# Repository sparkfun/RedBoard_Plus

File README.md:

SparkFun RedBoard Plus
============================

[*SparkFun RedBoard Plus (DEV-18158)*](https://www.sparkfun.com/products/18158)

At SparkFun we continually like to innovate, update, and improve even when it comes to our very own development boards. The SparkFun RedBoard Plus is an Arduino-compatible development board that has everything you need in an Arduino Uno with *many* extra perks. The best part about the RedBoard Plus is that it utilizes our handy Qwiic Connect System which means no soldering or shields are required to connect it to the rest of your system!

We've applied every lesson we've learned about making a better Arduino Uno and created the RedBoard Plus! The SparkFun RedBoard Plus has all of the hardware peripherals you know and love: 22x Digital I/O pins with 6x PWM pins, 8x analog pins, UART, I<sup>2</sup>C, SPI, and external interrupts. We've also broken out the SDA, SCL and IOREF pins that showed up on the Arduino Uno R3 footprint, so the RedBoard Plus is compatible with future shields (if you choose to use them). Two additional analog pins are included for A6 and A7.

The USB-to-serial is now done with a *reversible* USB-C connector with through hole anchoring and the ubiquitous CH340G requiring fewer driver installs. The power portion of the RedBoard Plus has been optimized: we use the AP2112 3.3V voltage regulator to provide up to 600mA to daisy chain multiple Qwiic boards and sensors, with full thermal and reverse circuit protection, and added extra decoupling capacitance to increase the sensitivity of the ADC readings. We've also increased the PTC from 500mA to 2A. We've decreased the brightness of the power LED, pin 13 LED, and the TX/RX LEDs from blinding to just perfect.

We've included 3.3V voltage translation and a [Qwiic connector](https://www.sparkfun.com/qwiic) to the edge of the board to allow for quick and seamless connection to our ever-growing line of I<sup>2</sup>C based [Qwiic products](https://www.sparkfun.com/qwiic#products). Jumpers are included on the board for the A4 and A5 pins which are tied directly to the I<sup>2</sup>C bus and can be used to disconnect the logic level converters from the pins. 

For more advanced users we've added an I/O voltage switch also known as the "Red Squirrel" switch (because they are the one [who petitioned for the mod](https://www.sparkfun.com/products/retired/15296#comment-5d78452ec6a6ff5bfc77dba7)). Now you can easily select the GPIO voltage between 3.3V or 5V with just your finger. This is extremely handy if you have a shield or 3.3V sensitive devices, such as an SPI interface, that needs protecting. Worried about accidentally flipping the switch? A piece of tape will lock it in place!

We include clearly labeled PTH holes alongside the standard female headers. This makes it very easy to solder wires in place for a secure connection to make your project 'backpack safe' once you get it working. Solder pads are included on the bottom of the board for USB data pins D+/D- so you can embed your RedBoard Plus into a project and run an external USB connection. We've increased the height of the reset button. This doesn't sound like much, but everyone who's touched it loves the improvement. 

The SparkFun RedBoard Plus can be programmed over a USB-C cable using the Arduino IDE: Just plug in the board, select "**Arduino UNO**" from the board menu and you're ready to upload code! You can power the SparkFun RedBoard Plus over USB or through the barrel jack. The on-board power regulator can handle anything from 7VDC to 15VDC. Check out the related items below for a compatible wall-wart power supply.

Not sure which Arduino or Arduino-compatible board is right for you? Check out our [Arduino Buying Guide](https://www.sparkfun.com/arduino_guide)!

Repository Contents
-------------------
* **/Documentation** - Data sheets, additional product information
* **/Hardware** - Eagle design files (.brd, .sch)
* **/Production** - Production panel files (.brd)

Documentation
--------------
* **[Hookup Guide](https://learn.sparkfun.com/tutorials/1758)** - Basic hookup guide for the RedBoard Plus.

License Information
-------------------

This product is _**open source**_! 

Please review the LICENSE.md file for license information. 

If you have any questions or concerns on licensing, please contact technical support on our [SparkFun forums](https://forum.sparkfun.com/viewforum.php?f=152).

Distributed as-is; no warranty is given.

- Your friends at SparkFun.

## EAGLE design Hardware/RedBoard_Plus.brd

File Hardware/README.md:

SparkFun RedBoard Plus Design Files
=====================================

The .sch and .brd files hare are Eagle CAD schematic and PCB design files from SparkFun Electronics.
A freeware version of Eagle can be found [here](http://www.cadsoftusa.com/download-eagle/freeware/).

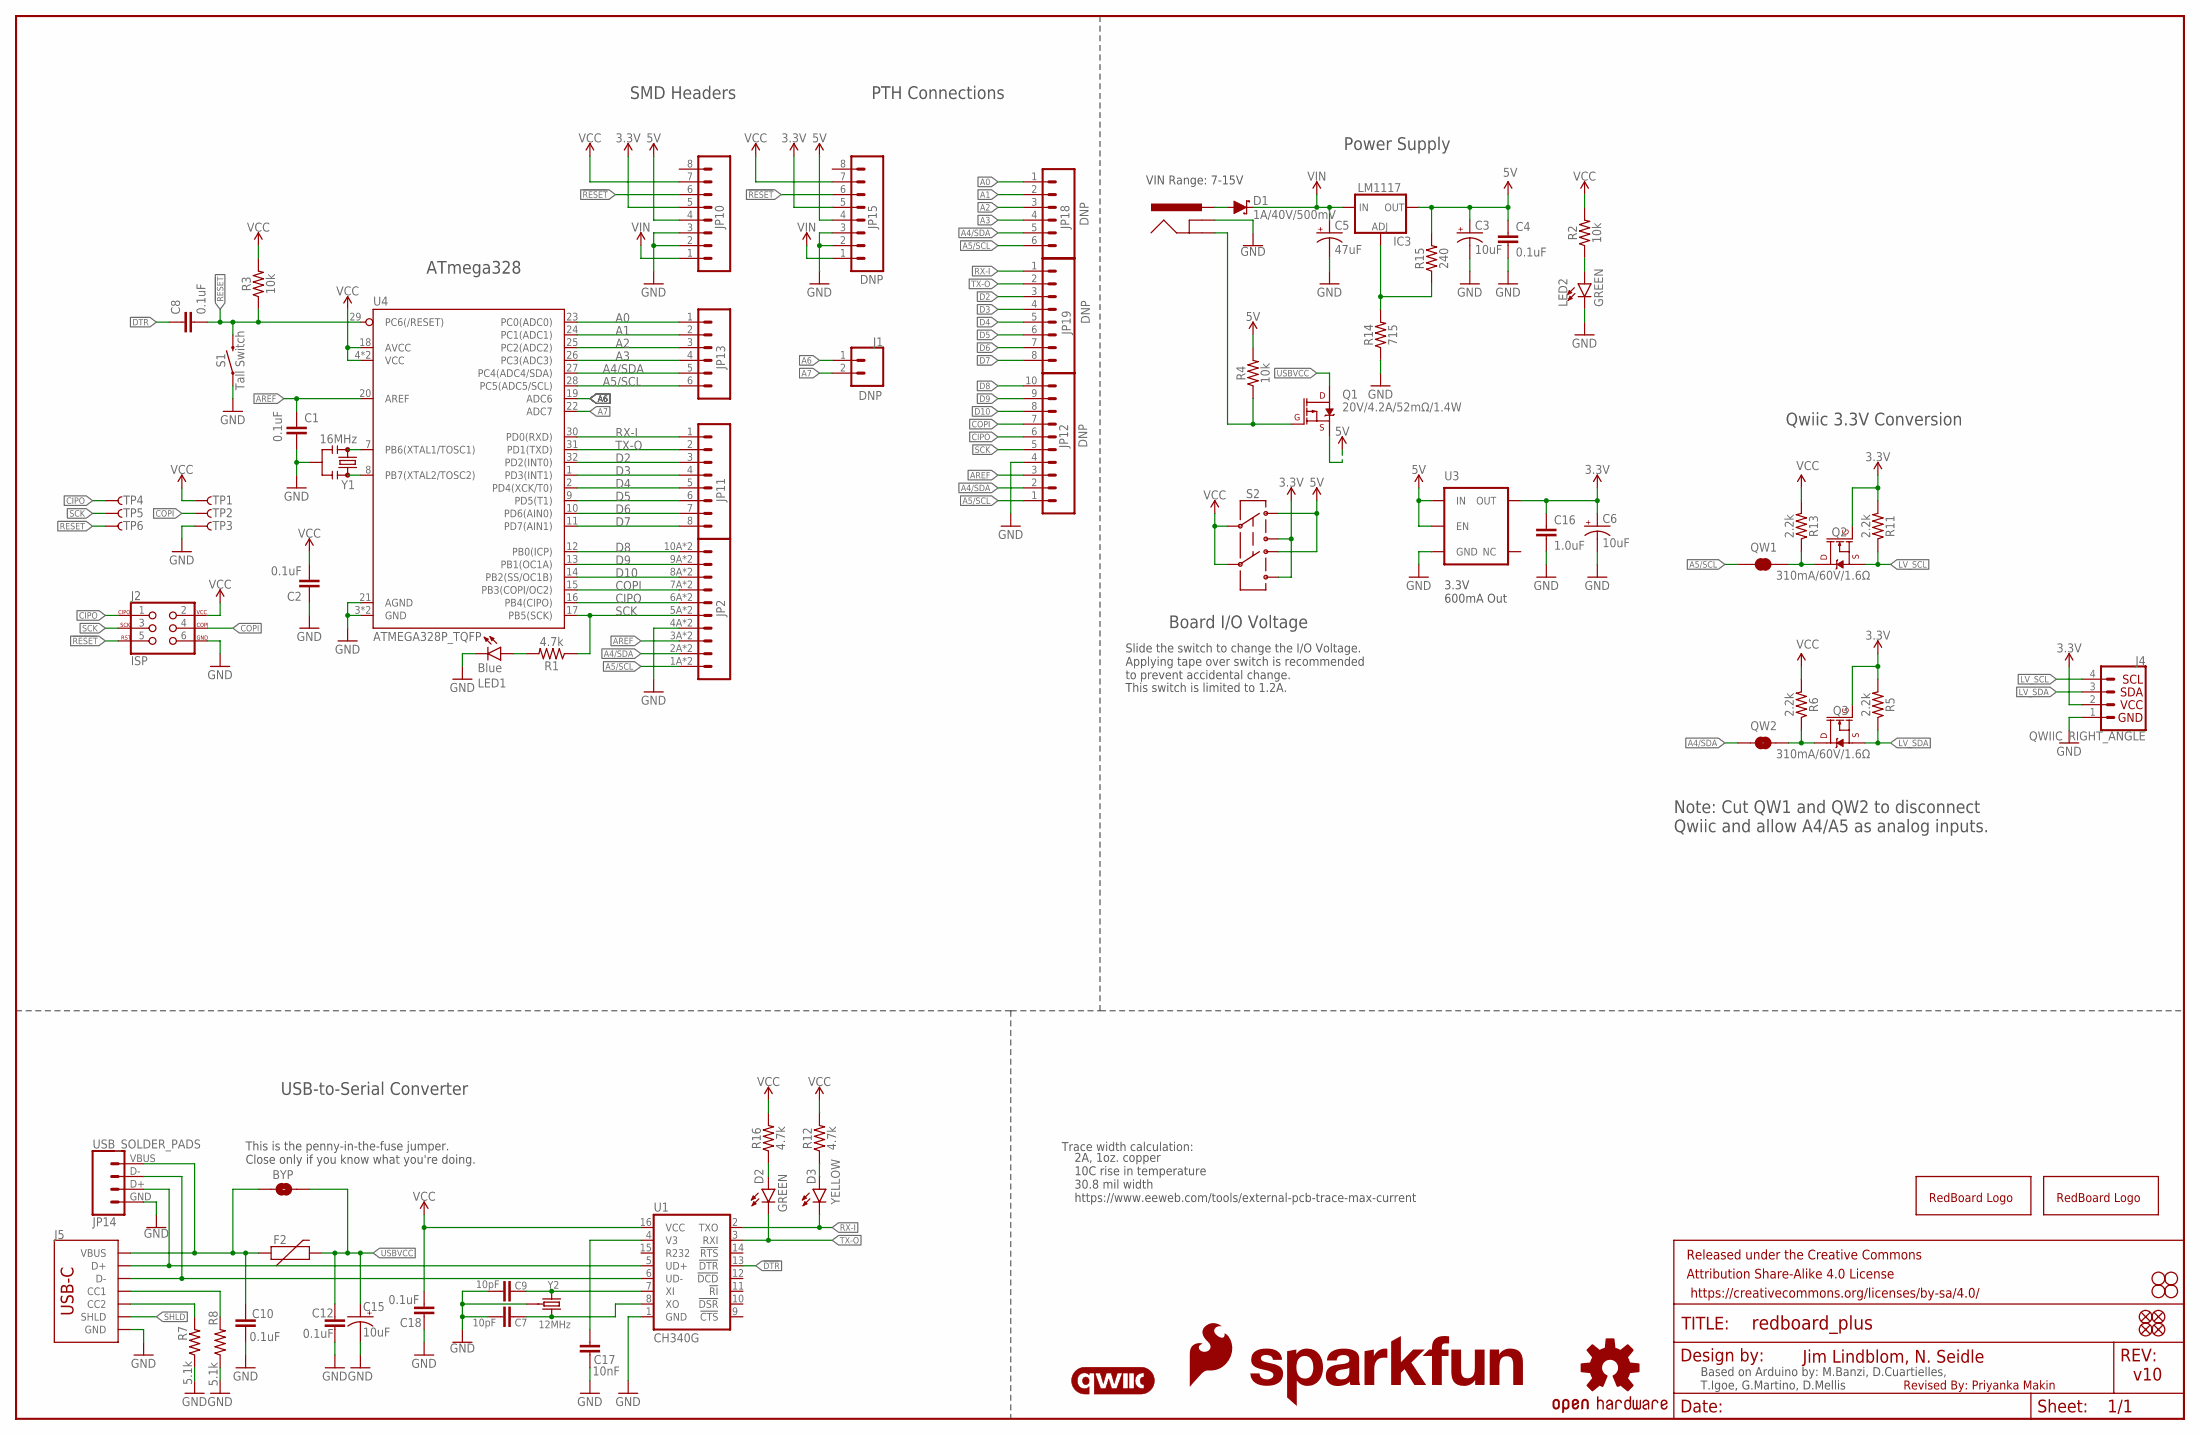
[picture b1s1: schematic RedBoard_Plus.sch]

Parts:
BYP: JUMPER-SMT_2_NO_SILK; SMT-JUMPER_2_NO_SILK
C1, C2, C4, C8, C10, C12, C18: 0.1uF; 0603
C3, C6, C15: 10uF; EIA3216
C5: 47uF; PANASONIC_D
C7, C9: 10pF; 0603
C16: 1.0uF; 0603
C17: 10nF; 0603
D1: 1A/40V/500mV; SMA-DIODE
D2: GREEN; LED-1206
D3: YELLOW; LED-1206-HIDDENSILK
F2: 6V/2A; 1210
FD1, FD2: FIDUCIAL1X2; FIDUCIAL-1X2
FRAME1: FRAME-LEDGER; CREATIVE_COMMONS
IC3: LM1117; SOT223
J1: DNP; 1X02_NO_SILK
J2: ISP; 2X3_SMT_POSTS
J3: 5.5x2.1mm Barrel; POWER_JACK_SMD
J4: QWIIC_RIGHT_ANGLE; JST04_1MM_RA
J5: USB Female Type C Connector; USB-C-16P-2LAYER-PADS
JP1: SFE_LOGO_NAME.1_INCH; SFE_LOGO_NAME_.1
JP2: CONN_10SMD_COMBO-FEMALE; 1X10_SMD_COMBINED
JP3, JP4, JP5, JP6: STAND-OFFTIGHT; STAND-OFF-TIGHT
JP7: SFE_LOGO_FLAME.1_INCH; SFE_LOGO_FLAME_.1
JP8, JP9: FIDUCIAL1X2; FIDUCIAL-1X2
JP10: CONN_08SMD-COMBO-FEMALE; 1X08_SMD_COMBINED
JP11: JP11; 1X08_SMD_COMBINED
JP12: DNP; 1X10_NO_SILK
JP13: CONN_06SMD-STRAIGHT-COMBO-FEMALE; 1X06_SMD_STRAIGHT_COMBO
JP14: USB_SOLDER_PADS; USB-SOLDER-PADS
JP15, JP19: DNP; 1X08_NO_SILK
JP18: DNP; 1X06_NO_SILK
LED1: Blue; LED-1206-HIDDENSILK
LED2: GREEN; LED-1206
LOGO1: QWIIC_LOGO_5MM; QWIIC_5MM
Q1: 20V/4.2A/52mΩ/1.4W; SOT23-3
Q2, Q3: 310mA/60V/1.6Ω; SOT323
QW1, QW2: JUMPER-SMT_2_NC_TRACE_SILK; SMT-JUMPER_2_NC_TRACE_SILK
R1, R12, R16: 4.7k; 0603
R2, R3, R4: 10k; 0603
R5, R6, R11, R13: 2.2k; 0603
R7, R8: 5.1k; 0603
R14: 715; 0603
R15: 240; 0603
S1: Tall Switch; TACTILE_SWITCH_SMD_5.2MM
S2: SWITCH-DPDT-SMD-AYZ0202; SWITCH_DPDT_SMD_AYZ0202
TP1, TP2, TP3, TP4, TP5, TP6: TP-3x5; PAD.03X.05
U1: CH340G; SO016
U3: 3.3V; SOT23-5
U4: ATMEGA328P_TQFP; TQFP32-08
U$1, U$3: REDBOARD_LOGO
U$16: OSHW-LOGOS; OSHW-LOGO-S
Y1: 16MHz; RESONATOR-SMD-3.2X1.3
Y2: 12MHz; CRYSTAL-SMD-3.2X2.5MM

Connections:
3.3V: C6.+, C16.1, J4.2, JP10.5, JP15.5, Q2.1 (G), Q3.1 (G), R5.2, R11.2, S2.1, S2.4, U3.5 (OUT)
5V: C3.+, C4.1, IC3.2 (OUT), IC3.4 (OUT), JP10.4, JP15.4, Q1.2 (S), R4.2, R15.2, S2.3, S2.6, U3.1 (IN), U3.3 (EN)
!DTR!: C8.1, U1.13 (!DTR)
!RESET: C8.2, J2.5, JP10.6, JP15.6, R3.1, S1.3 (2), S1.4 (2), TP6.P$1, U4.29 (PC6(/RESET))
A0: JP13.1, JP18.1, U4.23 (PC0(ADC0))
A1: JP13.2, JP18.2, U4.24 (PC1(ADC1))
A2: JP13.3, JP18.3, U4.25 (PC2(ADC2))
A3: JP13.4, JP18.4, U4.26 (PC3(ADC3))
A4/SDA: JP2.2A (2), JP2.2B (2), JP12.2, JP13.5, JP18.5, QW2.1, U4.27 (PC4(ADC4/SDA))
A5/SCL: JP2.1A (1), JP2.1B (1), JP12.1, JP13.6, JP18.6, QW1.1, U4.28 (PC5(ADC5/SCL))
A6: J1.1, U4.19 (ADC6)
A7: J1.2, U4.22 (ADC7)
AREF: C1.1, JP2.3A (3), JP2.3B (3), JP12.3, U4.20 (AREF)
CC1: J5.A5 (CC1), R8.2
CC2: J5.B5 (CC2), R7.2
CIPO: J2.1, JP2.6A (6), JP2.6B (6), JP12.6, TP4.P$1, U4.16 (PB4(CIPO))
COPI: J2.4, JP2.7A (7), JP2.7B (7), JP12.7, TP2.P$1, U4.15 (PB3(COPI/OC2))
D2: JP11.3, JP19.3, U4.32 (PD2(INT0))
D3: JP11.4, JP19.4, U4.1 (PD3(INT1))
D4: JP11.5, JP19.5, U4.2 (PD4(XCK/T0))
D5: JP11.6, JP19.6, U4.9 (PD5(T1))
D6: JP11.7, JP19.7, U4.10 (PD6(AIN0))
D7: JP11.8, JP19.8, U4.11 (PD7(AIN1))
D8: JP2.10A (10), JP2.10B (10), JP12.10, U4.12 (PB0(ICP))
D9: JP2.9A (9), JP2.9B (9), JP12.9, U4.13 (PB1(OC1A))
D10: JP2.8A (8), JP2.8B (8), JP12.8, U4.14 (PB2(SS/OC1B))
D+: J5.A6 (D+), J5.B6 (D+), JP14.D+ (3), U1.5 (UD+)
D-: J5.A7 (D-), J5.B7 (D-), JP14.D- (2), U1.6 (UD-)
GND: C1.2, C2.1, C3.-, C4.2, C5.-, C6.-, C7.2, C9.2, C10.2, C12.2, C15.-, C16.2, C17.2, C18.2, J2.6, J3.GND (GNDBREAK), J4.1, J5.GND, J5.GND2 (GND), JP2.4A (4), JP2.4B (4), JP10.2, JP10.3, JP12.4, JP14.GND (4), JP15.2, JP15.3, LED1.C, LED2.C, R7.1, R8.1, R14.1, S1.1, S1.2 (1), TP3.P$1, U1.1 (GND), U3.2 (GND), U4.3 (GND), U4.5 (GND), U4.21 (AGND), Y1.2, Y2.2 (GND), Y2.4 (GND)
INSERT: J3.P$4 (GND), Q1.1 (G), R4.1
LV_SCL: J4.4, Q2.2 (S), R11.1
LV_SDA: J4.3, Q3.2 (S), R5.1
unnamed: LED1.A, R1.2
unnamed: LED2.A, R2.1
unnamed: U4.7 (PB6(XTAL1/TOSC1)), Y1.1
unnamed: U4.8 (PB7(XTAL2/TOSC2)), Y1.3
unnamed: D2.A, R16.1
unnamed: C17.1, U1.4 (V3)
unnamed: Q2.3 (D), QW1.2, R13.1
unnamed: C9.1, U1.7 (XI), Y2.1
unnamed: D3.A, R12.1
unnamed: C7.1, U1.8 (XO), Y2.3 (2)
unnamed: IC3.1 (ADJ), R14.2, R15.1
unnamed: Q3.3 (D), QW2.2, R6.1
PWRIN: D1.A, J3.VIN0 (PWR)
RX-I: D3.C, JP11.1, JP19.1, U1.2 (TXO), U4.30 (PD0(RXD))
SCK: J2.3, JP2.5A (5), JP2.5B (5), JP12.5, R1.1, TP5.P$1, U4.17 (PB5(SCK))
SHLD: J5.SHLD1 (SHLD), J5.SHLD2 (SHLD), J5.SHLD3 (SHLD), J5.SHLD4 (SHLD)
TX-O: D2.C, JP11.2, JP19.2, U1.3 (RXI), U4.31 (PD1(TXD))
USBVCC: BYP.2, C12.1, C15.+, F2.2, Q1.3 (D)
VCC: C2.2, C18.1, J2.2, JP10.7, JP15.7, R2.2, R3.2, R6.2, R12.2, R13.2, R16.2, S2.2, S2.5, TP1.P$1, U1.16 (VCC), U4.4 (VCC), U4.6 (VCC), U4.18 (AVCC)
VIN: C5.+, D1.C, IC3.3 (IN), JP10.1, JP15.1
VUSB: BYP.1, C10.1, F2.1, J5.VBUS1 (VBUS), J5.VBUS2 (VBUS), JP14.VBUS (1)

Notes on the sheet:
Power Supply
ATmega328
USB-to-Serial Converter
Based on Arduino by: M.Banzi, D.Cuartielles, T.Igoe, G.Martino, D.Mellis
Jim Lindblom, N. Seidle
v10
VIN Range: 7-15V
3.3V 600mA Out
Board I/O Voltage
Slide the switch to change the I/O Voltage. Applying tape over switch is recommended to prevent accidental change.
Qwiic 3.3V Conversion
Note: Cut QW1 and QW2 to disconnect Qwiic and allow A4/A5 as analog inputs.
This is the penny-in-the-fuse jumper. Close only if you know what you're doing.
Trace width calculation:
2A, 1oz. copper 10C rise in temperature 30.8 mil width https://www.eeweb.com/tools/external-pcb-trace-max-current
This switch is limited to 1.2A.
PTH Connections
SMD Headers
Revised By: Priyanka Makin

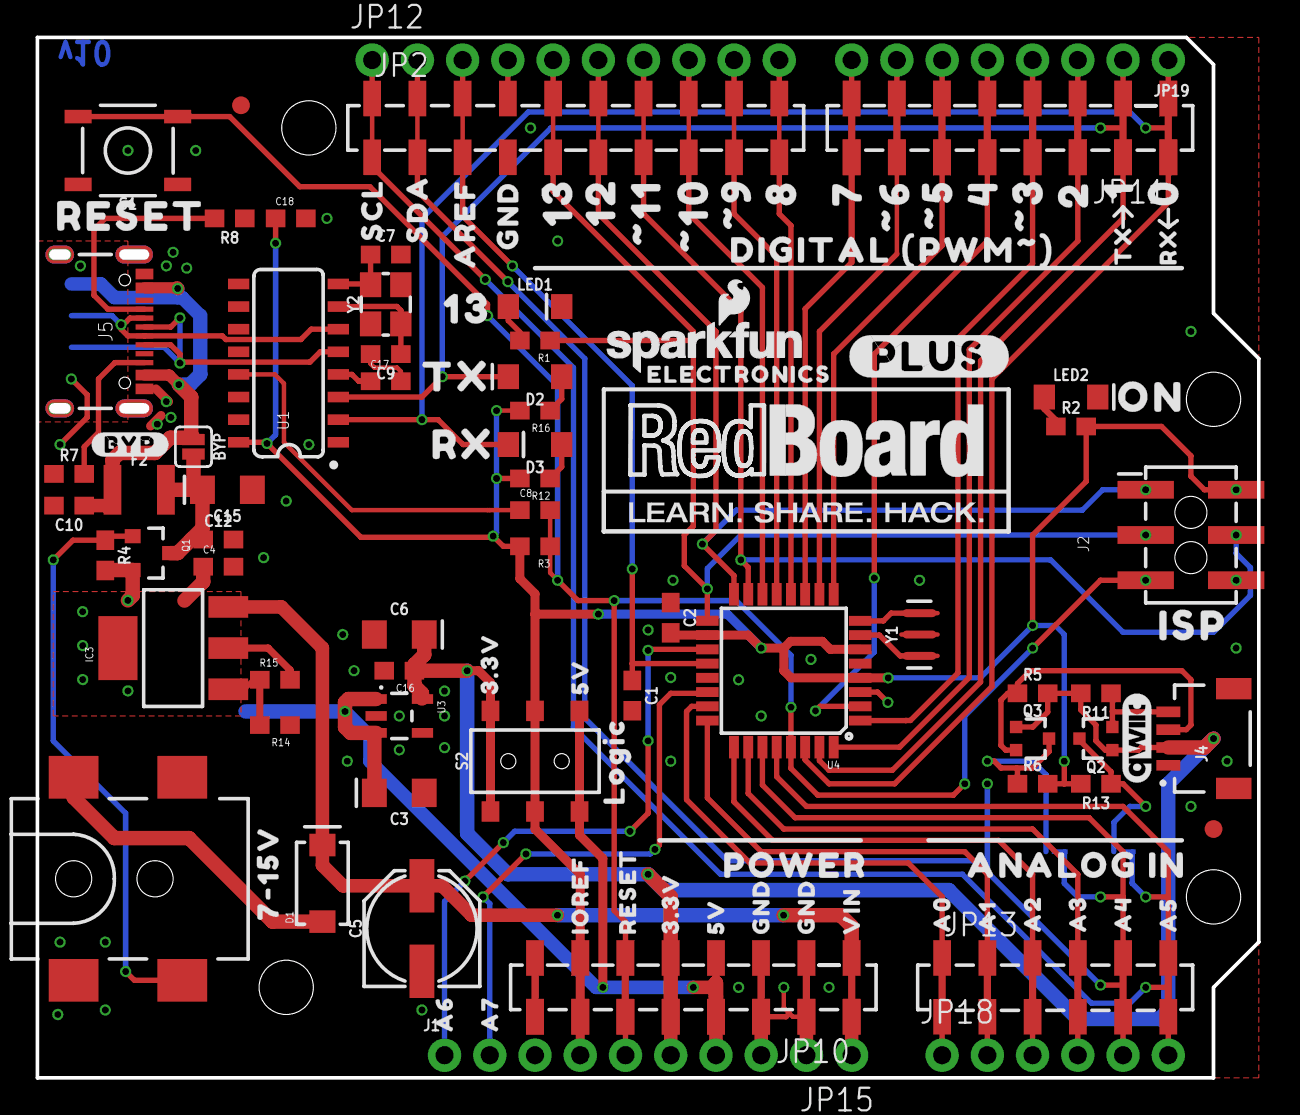
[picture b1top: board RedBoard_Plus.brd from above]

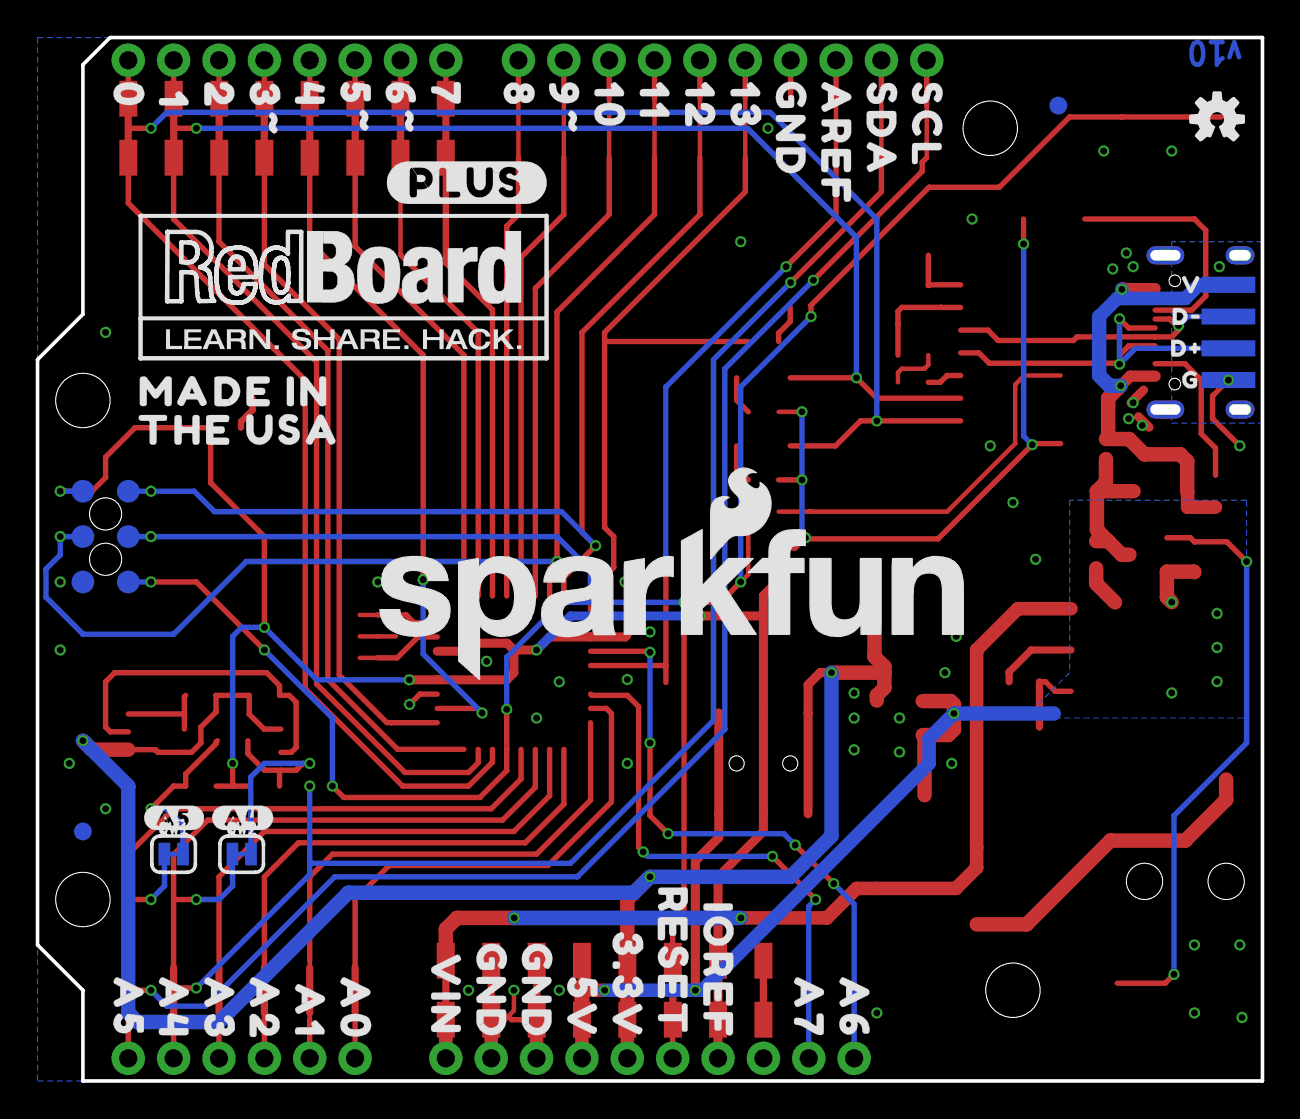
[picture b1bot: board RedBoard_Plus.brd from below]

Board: 2 copper layers, 68.6 x 58.4 mm, 179 parts (57 on the bottom side), 53 nets.

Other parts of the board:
U$2: _D#0
U$4: V0
U$10: G0
U$11: LOGIC0
U$12: D#0
U$13, U$95: _RESET0
U$14: #BYP#0
U$17: 7#15V0
U$18: _AREF0
U$19: _SCL0
U$20: _SDA0
U$22, U$77: 130
U$23, U$76: 120
U$24: #110
U$25: #100
U$26: #90
U$27, U$72: 80
U$28, U$71: 70
U$29: #60
U$30: #50
U$31, U$68: 40
U$32: #30
U$33, U$66: 20
U$34, U$65: 10
U$35, U$64: 00
U$36: TX0
U$37: RX0
U$38: DIGITAL_##PWM####_0
U$39: 13_0
U$40: _TX0
U$41: _RX0
U$42: _GND0
U$43, U$51: 3#3V0
U$44, U$52: 5V0
U$45: ON0
U$46: ISP0
U$47: POWER0
U$48: ANALOG_IN0
U$49: IOREF0
U$50: RESET0
U$53, U$54: GND0
U$55: VIN0
U$56: A00
U$57: A10
U$58: A20
U$59: A30
U$60: A40
U$61: A50
U$62: A60
U$63: A70
U$67: 3#0
U$69: 5#0
U$70: 6#0
U$73: 9#0
U$74: 100
U$75: 110
U$78: SFE_LOGO_NAME_.3
U$79: AREF0
U$80: SDA0
U$81: SCL0
U$82: MADE_IN0
U$83: THE_USA0
U$84: _A40
U$85, U$99, U$107: _GND_0
U$86: _A30
U$87: _A20
U$88: _A10
U$89: _A00
U$90: _VIN0
U$93: _5V0
U$94: _3#3V0
U$96: _IOREF0
U$97: _A60
U$98: _A70
U$100, U$103: #PLUS#0
U$101: SFE_LOGO_FLAME_.2
U$102: _A50
U$104: ELECTRONICS0
U$105: #A4#0
U$106: #A5#0

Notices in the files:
parts and their libraries:
SparkFun-Aesthetics: Licensing: CC v3.0 Share-Alike You are welcome to use this library for commercial purposes.
SparkFun-DiscreteSemi: Licensing: Creative Commons ShareAlike 4.0 International - https://creativecommons.org/licenses/by-sa/4.0
SparkFun-Aesthetics: Released under the Creative Commons
